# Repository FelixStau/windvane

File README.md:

# NMEA 2000 Windvane

In progress ...

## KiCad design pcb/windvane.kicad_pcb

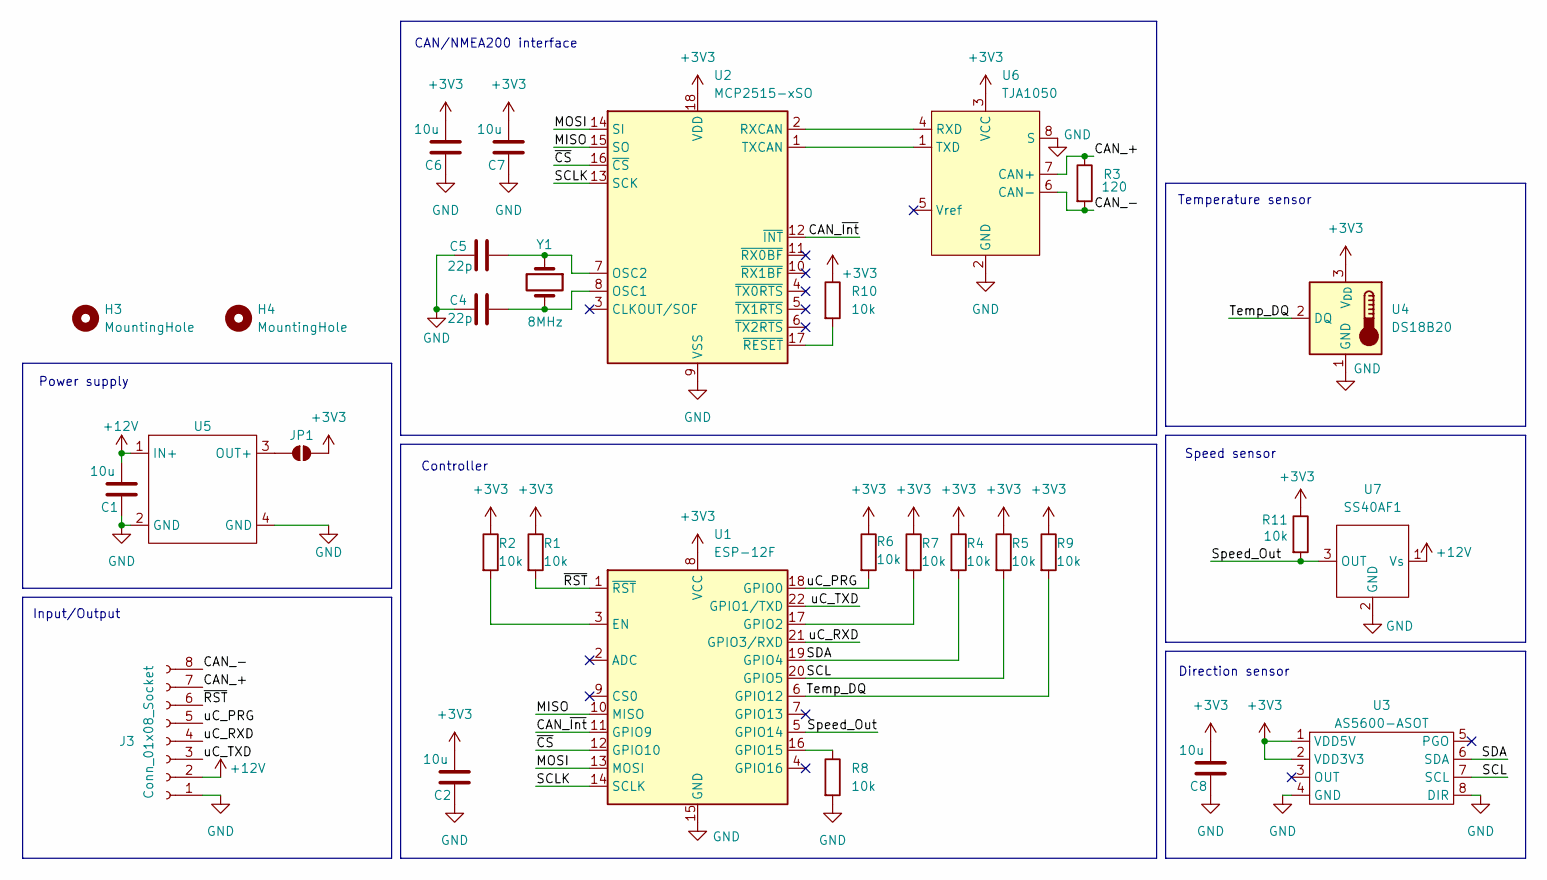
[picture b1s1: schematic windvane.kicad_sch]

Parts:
C1, C2, C6, C7, C8: 10u; C_0805_2012Metric
C4, C5: 22p; C_0805_2012Metric
H3, H4: MountingHole; MountingHole_2.2mm_M2
J3: Conn_01x08_Socket; CON_532610871
JP1: SolderJumper_2_Open; SolderJumper-2_P1.3mm_Open_Pad1.0x1.5mm
R1, R2, R4, R5, R6, R7, R8, R9, R10, R11: 10k; R_0805_2012Metric
R3: 120; R_0805_2012Metric
U1: ESP-12F; ESP-12E
U2: MCP2515-xSO; SOIC-18W_7.5x11.6mm_P1.27mm
U3: AS5600-ASOT; SOIC-8_3.9x4.9mm_P1.27mm
U4: DS18B20; TO-92_Inline
U5: MiniStepDownConverter
U6: TJA1050; SOIC-8_3.9x4.9mm_P1.27mm
U7: SS40AF1; TO-92L_Inline
Y1: 8MHz; Crystal_HC49-4H_Vertical

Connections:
+3V3: C2.2, C6.2, C7.2, C8.2, JP1.2 (B), R1.1, R2.1, R4.1, R5.1, R6.1, R7.1, R9.1, R10.1, R11.1, U1.8 (VCC), U2.18 (VDD), U3.1 (VDD5V), U3.2 (VDD3V3), U4.3 (V_{DD}), U6.3 (VCC)
+12V: C1.2, J3.2, U5.1 (IN+), U7.1 (Vs)
/CAN_+: J3.7, R3.1, U6.7 (CAN+)
/CAN_-: J3.8, R3.2, U6.6 (CAN-)
/CAN_~Int: U1.11 (GPIO9), U2.12 (~INT)
/MISO: U1.10 (MISO), U2.15 (SO)
/MOSI: U1.13 (MOSI), U2.14 (SI)
/SCL: R5.2, U1.20 (GPIO5), U3.7 (SCL)
/SCLK: U1.14 (SCLK), U2.13 (SCK)
/SDA: R4.2, U1.19 (GPIO4), U3.6 (SDA)
/Speed_Out: R11.2, U1.5 (GPIO14), U7.3 (OUT)
/Temp_DQ: R9.2, U1.6 (GPIO12), U4.2 (DQ)
/uC_PRG: J3.5, R6.2, U1.18 (GPIO0)
/uC_RXD: J3.4, U1.21 (GPIO3/RXD)
/uC_TXD: J3.3, U1.22 (GPIO1/TXD)
/~CS: U1.12 (GPIO10), U2.16 (~CS)
/~RST: J3.6, R1.2, U1.1 (~RST)
GND: C1.1, C2.1, C4.1, C5.1, C6.1, C7.1, C8.1, J3.1, R8.2, U1.15 (GND), U2.9 (VSS), U3.4 (GND), U3.8 (DIR), U4.1 (GND), U5.2 (GND), U5.4 (GND), U6.2 (GND), U6.8 (S), U7.2 (GND)
unnamed: JP1.1 (A), U5.3 (OUT+)
unnamed: R2.2, U1.3 (EN)
unnamed: R7.2, U1.17 (GPIO2)
unnamed: R8.1, U1.16 (GPIO15)
unnamed: C4.2, U2.8 (OSC1), Y1.2
unnamed: C5.2, U2.7 (OSC2), Y1.1
unnamed: U2.2 (RXCAN), U6.4 (RXD)
unnamed: U2.1 (TXCAN), U6.1 (TXD)
unnamed: R10.2, U2.17 (~RESET)

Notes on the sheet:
Controller
CAN/NMEA200 interface
Temperature sensor
Direction sensor
Power supply
Speed sensor
Input/Output

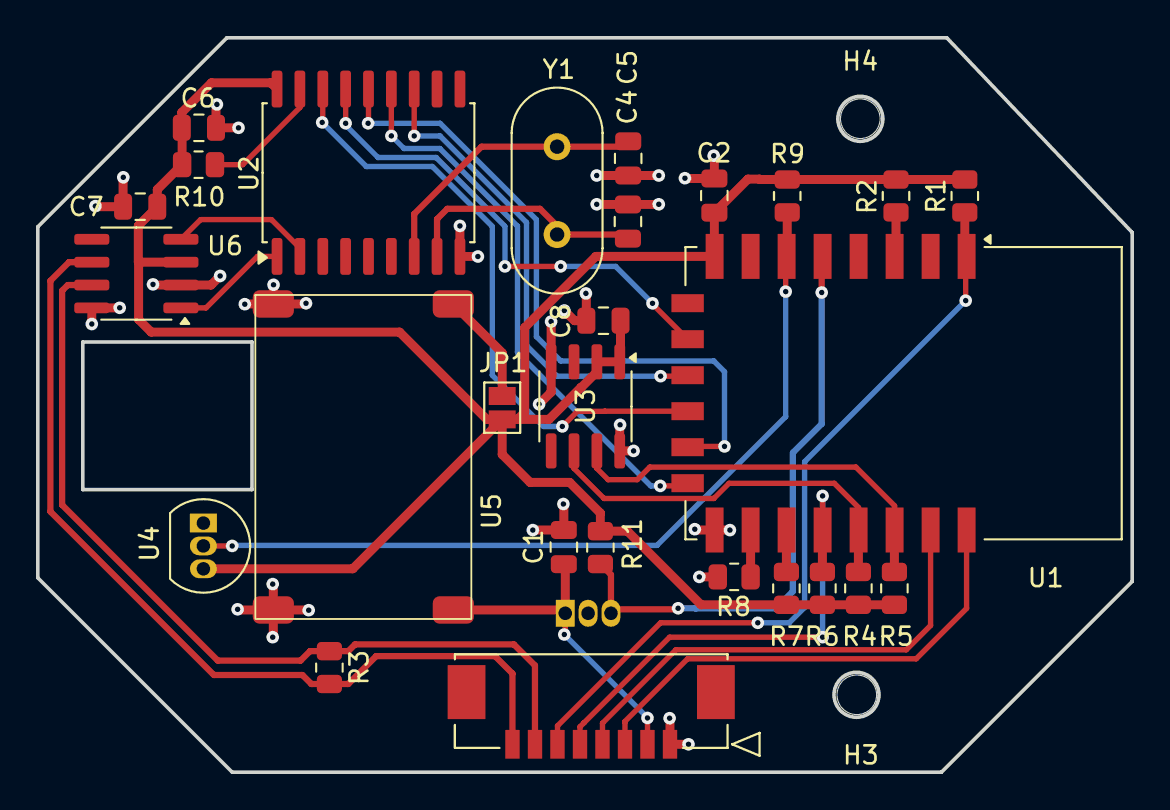
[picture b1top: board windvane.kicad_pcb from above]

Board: 2 copper layers, 60.8 x 40.8 mm, 30 parts (1 on the bottom side), 27 nets.

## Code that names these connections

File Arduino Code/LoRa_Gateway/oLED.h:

// 1-channel LoRa Gateway for ESP8266
// Copyright (c) 2016, 2017, 2018 Maarten Westenberg version for ESP8266
// Version 5.3.3
// Date: 2018-08-25
//
// based on work done by Thomas Telkamp for Raspberry PI 1ch gateway
// and many others.
//
// All rights reserved. This program and the accompanying materials
// are made available under the terms of the MIT License
// which accompanies this distribution, and is available at
// https://opensource.org/licenses/mit-license.php
//
// NO WARRANTY OF ANY KIND IS PROVIDED
//
// Author: Maarten Westenberg (mw12554@hotmail.com)
//
// This file contains a number of compile-time settings and definitions for OLED support.
//
// ----------------------------------------------------------------------------------------

// OLEDs dupported by this program must be I2C.
// This is because we do not want any diisturbance in the SPI area
// which is also interfacing the LORA tranceiver.
//
// The following OLDs are supported:
// 0. No OLED connected
// 1. 0.9" OLED (cheap)
// 2. 1.3" OLED with much better and larger display

#if OLED>=1										// If OLED is used

// --------------------------------------------------------	
// Define the different PIN's used for SCL/SDA for each arch.
//
#if _PIN_OUT==1									// HALLARD
#define OLED_SCL 5								// GPIO5 / D1
#define OLED_SDA 4								// GPIO4 / D2

#elif _PIN_OUT==2								// COMRESULT				
#define OLED_SCL 0								// GPIO0 / D3
#define OLED_SDA 2								// GPIO2 / D4

#elif _PIN_OUT==4								// TTGO (onboard version used, also for DIY)
#define OLED_SCL 15								// GPIO15 / 
#define OLED_SDA 4								// GPIO4 / 
#define OLED_RST 16								// Reset pin (Some OLED displays do not have it)

#elif _PIN_OUT==6                // Heltec (onboard version used, also for DIY)
#define OLED_SCL 15               // GPIO15 / 
#define OLED_SDA 4                // GPIO4 / 
#define OLED_RST 16               // Reset pin (Some OLED displays do not have it)

#endif


// --------------------------------------------------------	
// Define the different OLED versions
//
#if OLED==1
#include "SSD1306.h"
#define OLED_ADDR 0x3C							// Default 0x3C for 0.9", for 1.3" it is 0x78
SSD1306  display(OLED_ADDR, OLED_SDA, OLED_SCL);// i2c ADDR & SDA, SCL on wemos
#endif

// This is an 1.3" OLED display which is running on I2C
#if OLED==2
#include "SH1106.h"
#define OLED_ADDR 0x3C							// Default 0x3C for 1.3" SH1106
SH1106  display(OLED_ADDR, OLED_SDA, OLED_SCL);	// i2c ADDR & SDA, SCL on wemos
#endif

#endif//OLED>=1

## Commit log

2021-05-31 Add LICENSE
2021-05-31 Update .gitlab-ci.yml file
2021-05-31 Add new directory
2021-06-30 New Android App
2021-07-01 Documentation
2021-07-01 Pictures
2021-07-01 Mods
2021-07-01 Add binarys
2021-07-01 Add source code
2021-07-01 Upload New File
2021-07-01 Add CAD file
2021-07-01 Add pictures
2021-07-01 Add gateway source code
2021-07-01 Add documentation
2021-07-01 Change Documentation
2021-07-01 Doku
2021-07-01 Docu
2021-08-03 New documentation
2021-08-19 Initial download
2021-08-19 Add firmware
2021-08-19 Change name
2021-08-20 New content
2021-08-20 Add new file
2021-08-24 Add data sheet
2021-09-02 New PCB board
2021-09-02 New data sheet
2021-09-02 add files
2021-11-18 Fusion360 CAD Files
2021-11-22 PCB with BME280
2021-11-22 Schematic with BME280
2021-11-22 Yachta board with BME280
2024-10-28 forked from https://gitlab.com/norbertwalter67/windsensor_yachta.git, cleanup, restructured
2024-10-28 deleted README
2024-10-29 schematic done, next up - layout
2024-10-31 place & route
2024-11-01 routing - done, next up - review
2024-12-01 added stacktracer tool
2024-12-01 added unit tests to verify functionality of all components
2024-12-08 added test routines for mcp and NMEA200
2024-12-08 added esp12 datasheet
2024-12-08 bugfixing: connected esp reset to connector, corrected wrong pin assigment of RPM sensor, improved routing, remapped CAN interrupt to GPIO9
